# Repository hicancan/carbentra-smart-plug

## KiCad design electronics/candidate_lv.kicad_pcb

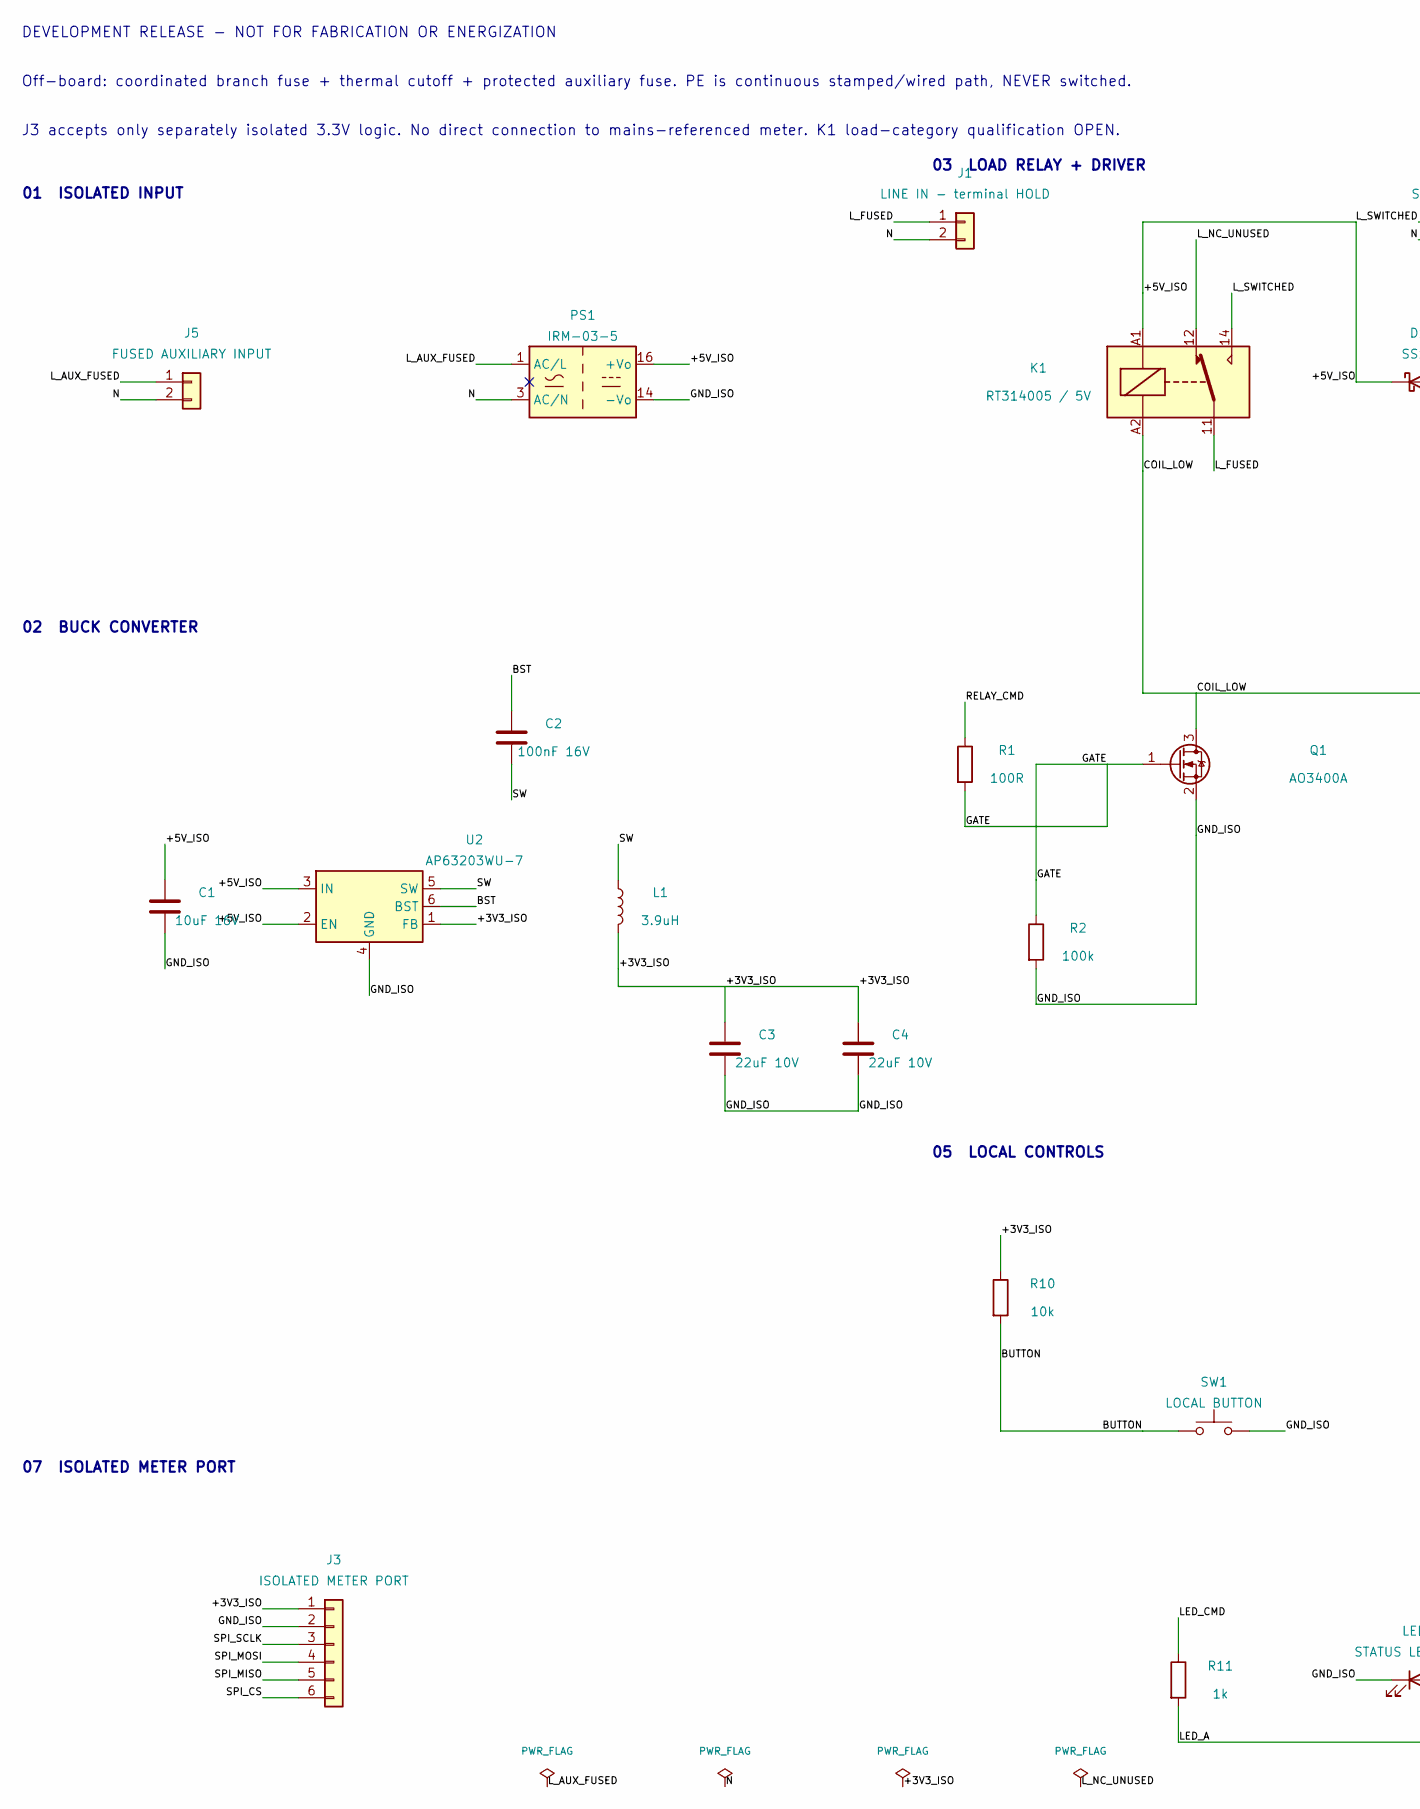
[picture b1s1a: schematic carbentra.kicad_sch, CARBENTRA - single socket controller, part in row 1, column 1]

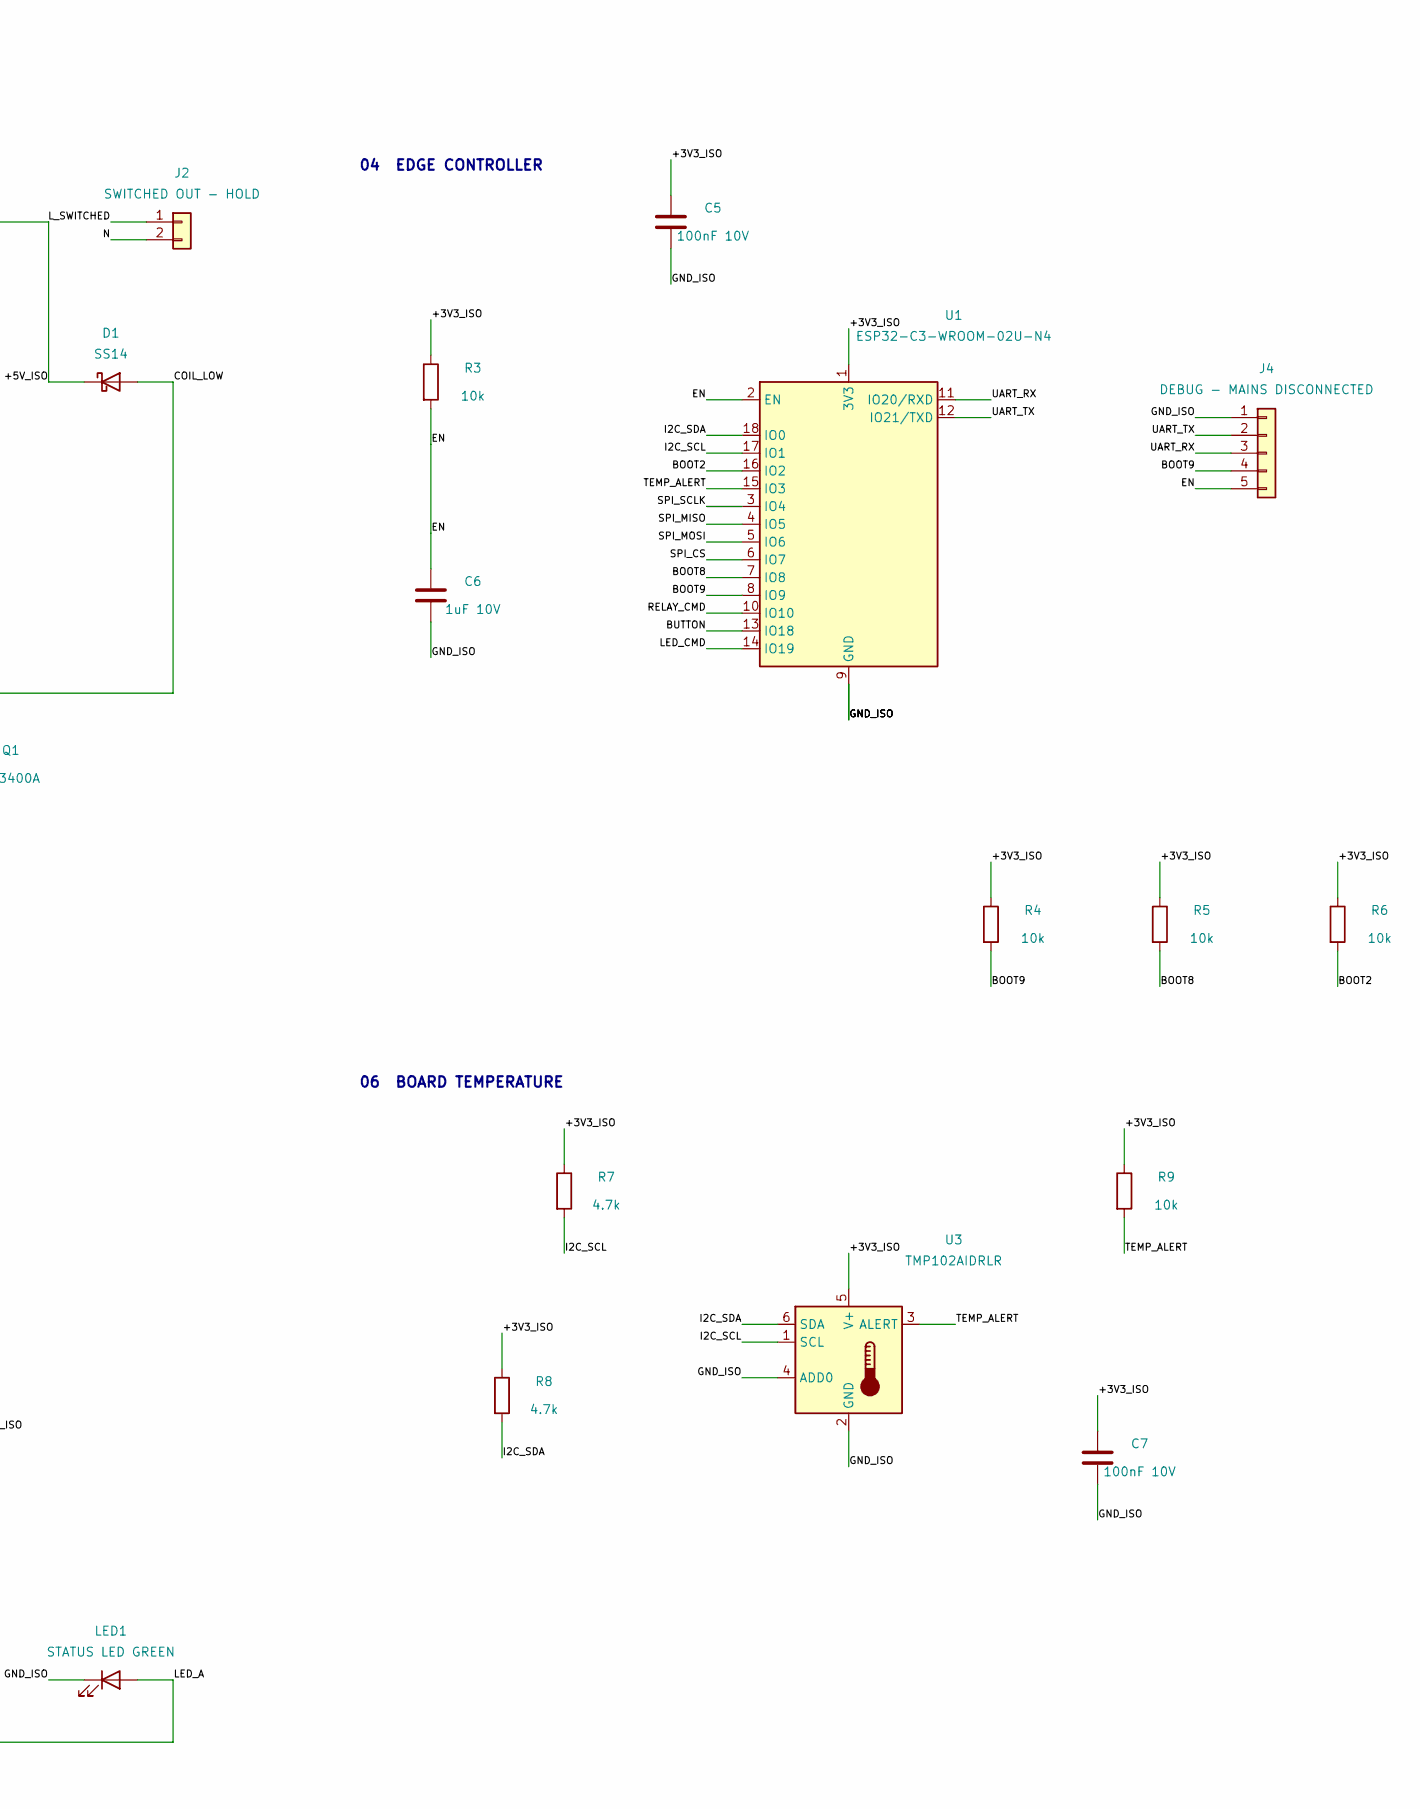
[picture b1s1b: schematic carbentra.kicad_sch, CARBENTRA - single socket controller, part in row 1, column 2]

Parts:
C1: 10uF 16V; C_0805_2012Metric
C2: 100nF 16V; C_0805_2012Metric
C3, C4: 22uF 10V; C_0805_2012Metric
C5, C7: 100nF 10V; C_0805_2012Metric
C6: 1uF 10V; C_0805_2012Metric
D1: SS14; D_SMA
J1: LINE IN - terminal HOLD; TerminalBlock_Phoenix_MKDS-3-2-5.08_1x02_P5.08mm_Horizontal
J2: SWITCHED OUT - HOLD; TerminalBlock_Phoenix_MKDS-3-2-5.08_1x02_P5.08mm_Horizontal
J3: ISOLATED METER PORT; PinHeader_1x06_P2.54mm_Vertical
J4: DEBUG - MAINS DISCONNECTED; PinHeader_1x05_P2.54mm_Vertical
J5: FUSED AUXILIARY INPUT; TerminalBlock_Phoenix_MKDS-3-2-5.08_1x02_P5.08mm_Horizontal
K1: RT314005 / 5V; Relay_SPDT_Schrack-RT1-16A-FormC_RM5mm
L1: 3.9uH; L_Bourns-SRN4018
LED1: STATUS LED GREEN; LED_D3.0mm
PS1: IRM-03-5; Converter_ACDC_MeanWell_IRM-03-xx_THT
Q1: AO3400A; SOT-23
R1: 100R; R_0603_1608Metric
R2: 100k; R_0603_1608Metric
R3, R4, R5, R6, R9, R10: 10k; R_0603_1608Metric
R7, R8: 4.7k; R_0603_1608Metric
R11: 1k; R_0603_1608Metric
SW1: LOCAL BUTTON; SW_PUSH_6mm
U1: ESP32-C3-WROOM-02U-N4; ESP32-C3-WROOM-02U
U2: AP63203WU-7; TSOT-23-6
U3: TMP102AIDRLR; SOT-563

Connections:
+3V3_ISO: C3.1, C4.1, C5.1, C7.1, J3.1, L1.2, R3.1, R4.1, R5.1, R6.1, R7.1, R8.1, R9.1, R10.1, U1.1 (3V3), U2.1 (FB), U3.5 (V+)
+5V_ISO: C1.1, D1.1 (K), K1.A1, PS1.16 (+Vo), U2.2 (EN), U2.3 (IN)
BOOT2: R6.2, U1.16 (IO2)
BOOT8: R5.2, U1.7 (IO8)
BOOT9: J4.4, R4.2, U1.8 (IO9)
BST: C2.1, U2.6 (BST)
BUTTON: R10.2, SW1.1, U1.13 (IO18)
COIL_LOW: D1.2 (A), K1.A2, Q1.3 (D)
EN: C6.1, J4.5, R3.2, U1.2 (EN)
GATE: Q1.1 (G), R1.2, R2.1
GND_ISO: C1.2, C3.2, C4.2, C5.2, C6.2, C7.2, J3.2, J4.1, LED1.1 (K), PS1.14 (-Vo), Q1.2 (S), R2.2, SW1.2, U1.9 (GND), U1.19 (GND), U2.4 (GND), U3.2 (GND), U3.4 (ADD0)
I2C_SCL: R7.2, U1.17 (IO1), U3.1 (SCL)
I2C_SDA: R8.2, U1.18 (IO0), U3.6 (SDA)
LED_A: LED1.2 (A), R11.2
LED_CMD: R11.1, U1.14 (IO19)
L_AUX_FUSED: J5.1, PS1.1 (AC/L)
L_FUSED: J1.1, K1.11
L_NC_UNUSED: K1.12
L_SWITCHED: J2.1, K1.14
N: J1.2, J2.2, J5.2, PS1.3 (AC/N)
RELAY_CMD: R1.1, U1.10 (IO10)
SPI_CS: J3.6, U1.6 (IO7)
SPI_MISO: J3.5, U1.4 (IO5)
SPI_MOSI: J3.4, U1.5 (IO6)
SPI_SCLK: J3.3, U1.3 (IO4)
SW: C2.2, L1.1, U2.5 (SW)
TEMP_ALERT: R9.2, U1.15 (IO3), U3.3 (ALERT)
UART_RX: J4.3, U1.11 (IO20/RXD)
UART_TX: J4.2, U1.12 (IO21/TXD)

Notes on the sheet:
DEVELOPMENT RELEASE - NOT FOR FABRICATION OR ENERGIZATION
Off-board: coordinated branch fuse + thermal cutoff + protected auxiliary fuse. PE is continuous stamped/wired path, NEVER switched.
J3 accepts only separately isolated 3.3V logic. No direct connection to mains-referenced meter. K1 load-category qualification OPEN.
01 ISOLATED INPUT
02 BUCK CONVERTER
03 LOAD RELAY + DRIVER
04 EDGE CONTROLLER
05 LOCAL CONTROLS
06 BOARD TEMPERATURE
07 ISOLATED METER PORT

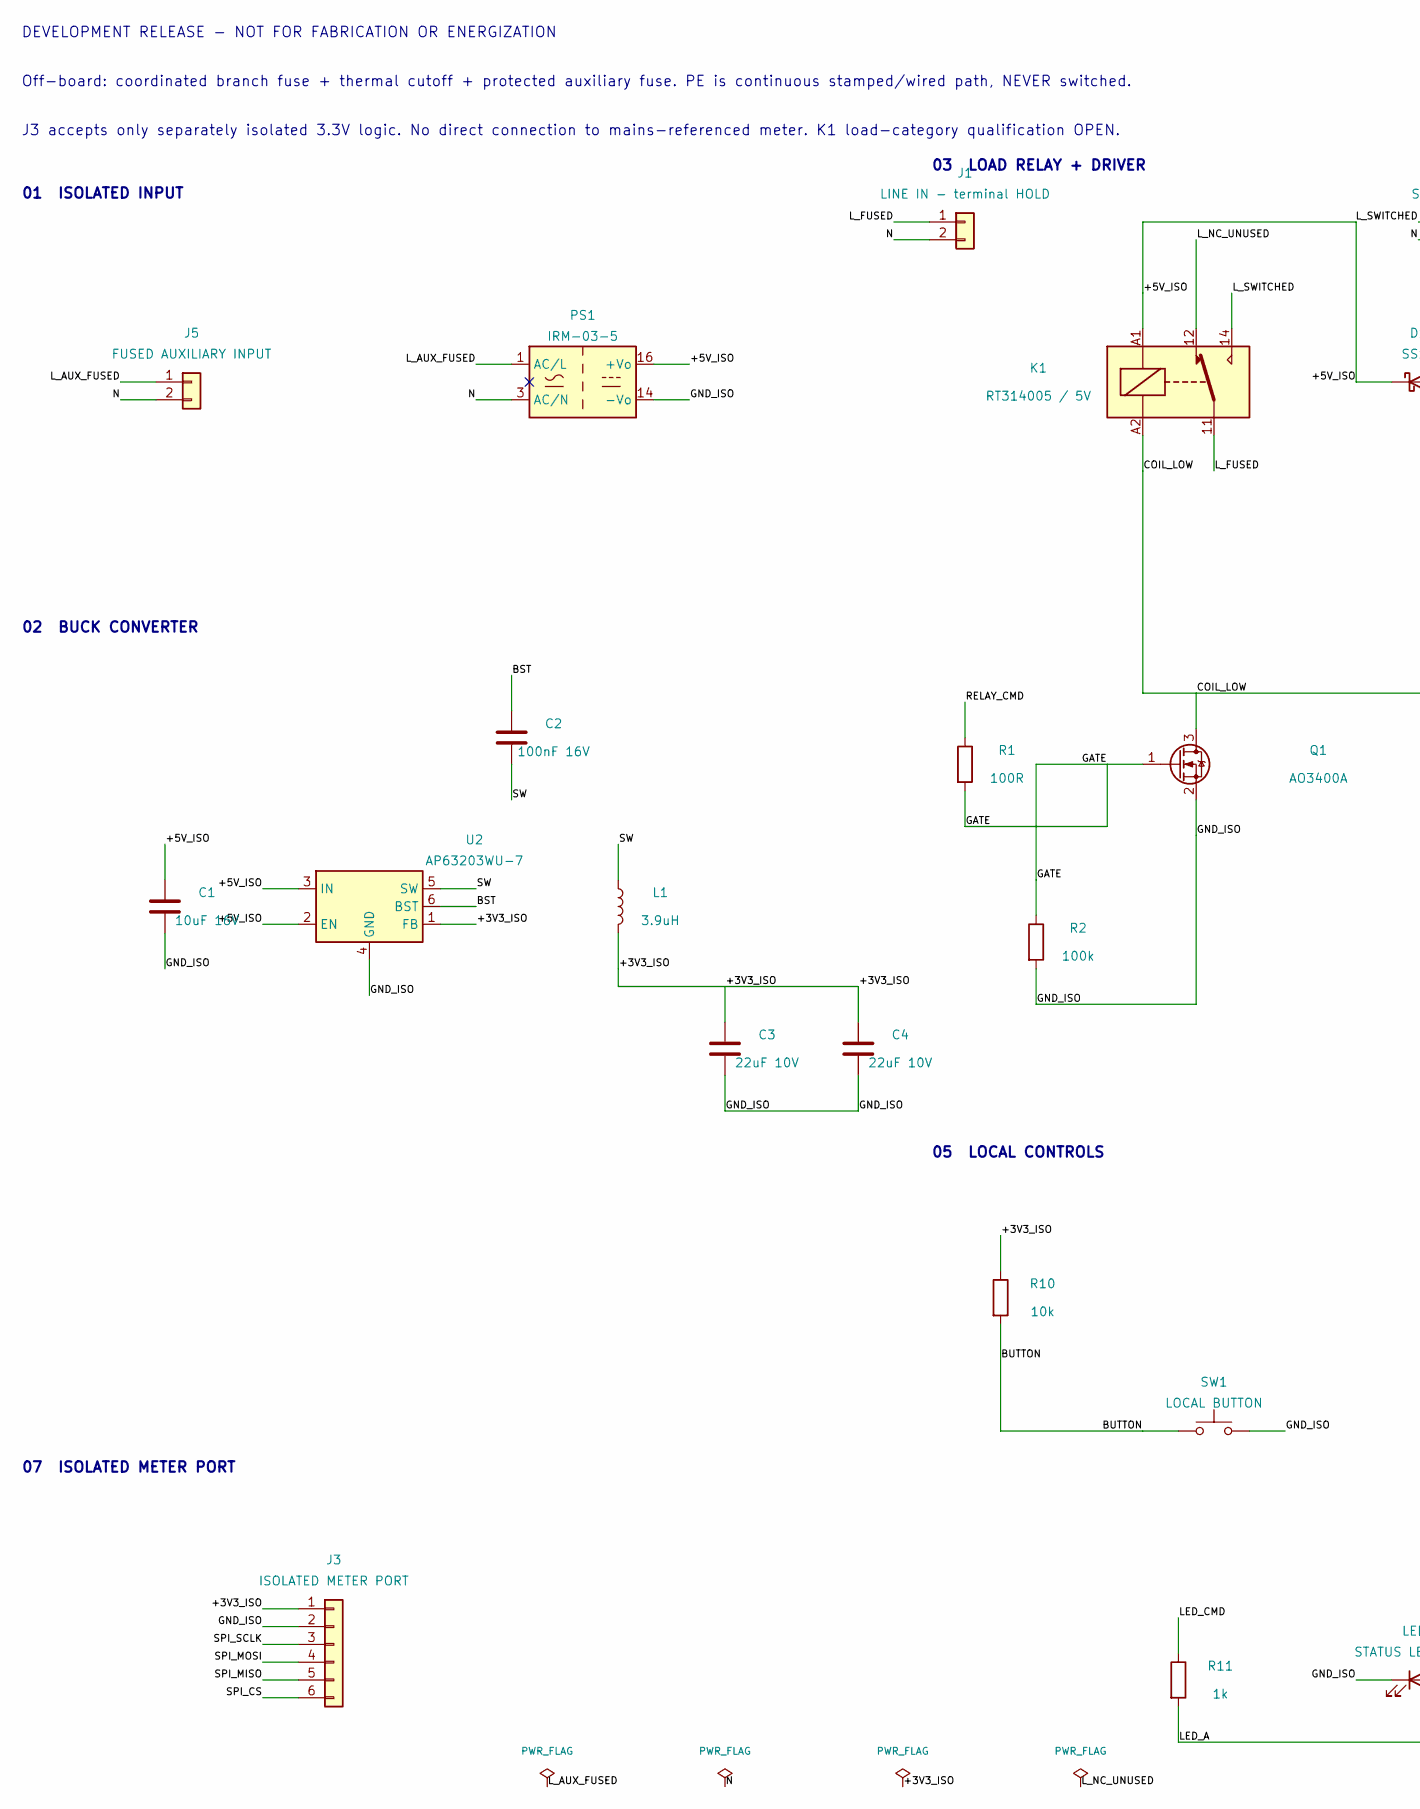
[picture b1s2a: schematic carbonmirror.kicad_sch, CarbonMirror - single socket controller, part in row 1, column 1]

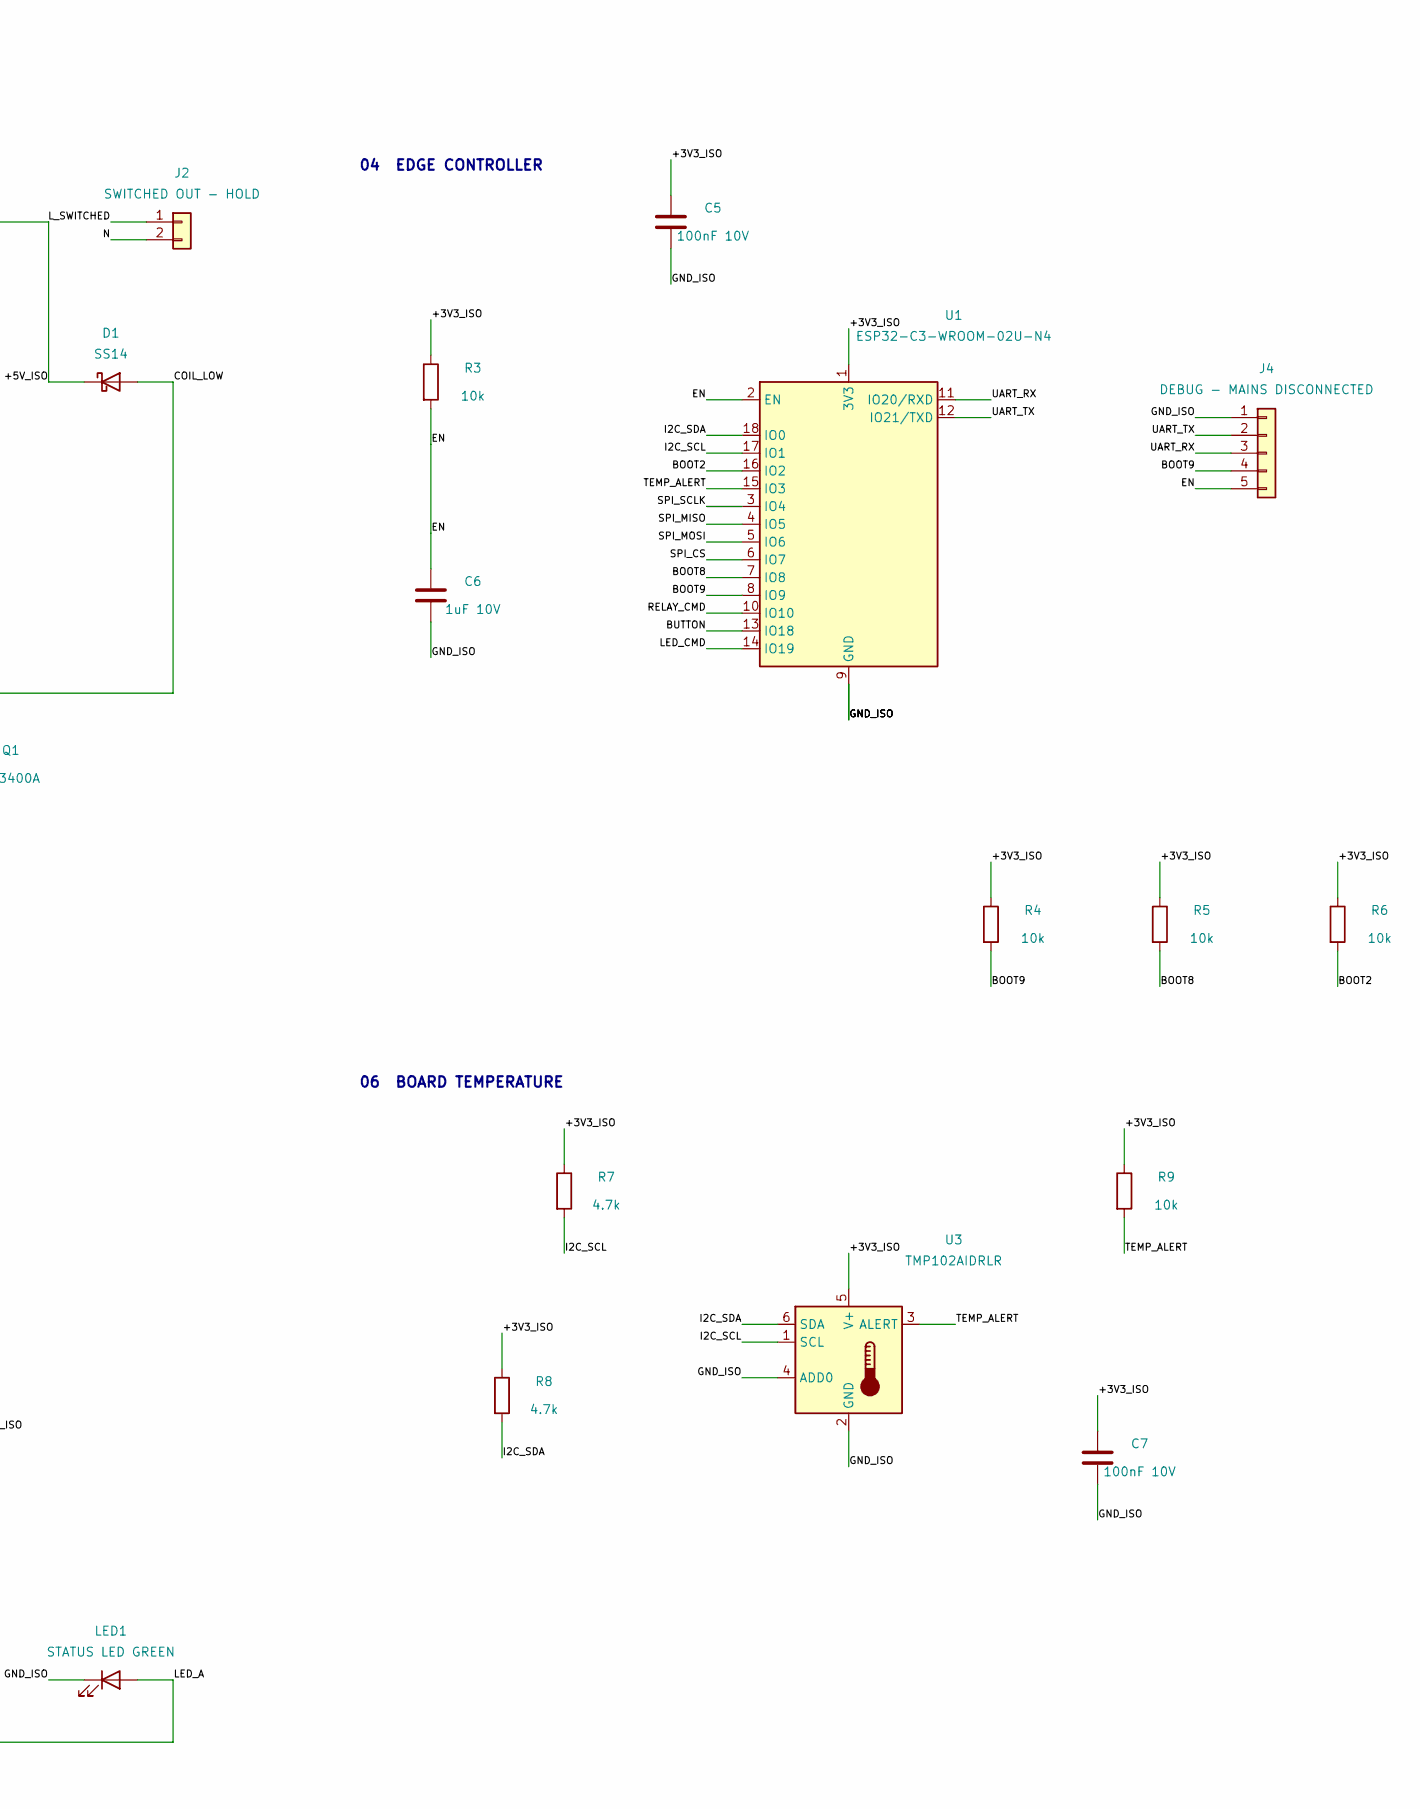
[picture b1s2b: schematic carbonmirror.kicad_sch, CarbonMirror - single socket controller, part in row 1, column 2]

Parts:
C1: 10uF 16V; C_0805_2012Metric
C2: 100nF 16V; C_0805_2012Metric
C3, C4: 22uF 10V; C_0805_2012Metric
C5, C7: 100nF 10V; C_0805_2012Metric
C6: 1uF 10V; C_0805_2012Metric
D1: SS14; D_SMA
J1: LINE IN - terminal HOLD; TerminalBlock_Phoenix_MKDS-3-2-5.08_1x02_P5.08mm_Horizontal
J2: SWITCHED OUT - HOLD; TerminalBlock_Phoenix_MKDS-3-2-5.08_1x02_P5.08mm_Horizontal
J3: ISOLATED METER PORT; PinHeader_1x06_P2.54mm_Vertical
J4: DEBUG - MAINS DISCONNECTED; PinHeader_1x05_P2.54mm_Vertical
J5: FUSED AUXILIARY INPUT; TerminalBlock_Phoenix_MKDS-3-2-5.08_1x02_P5.08mm_Horizontal
K1: RT314005 / 5V; Relay_SPDT_Schrack-RT1-16A-FormC_RM5mm
L1: 3.9uH; L_Bourns-SRN4018
LED1: STATUS LED GREEN; LED_D3.0mm
PS1: IRM-03-5; Converter_ACDC_MeanWell_IRM-03-xx_THT
Q1: AO3400A; SOT-23
R1: 100R; R_0603_1608Metric
R2: 100k; R_0603_1608Metric
R3, R4, R5, R6, R9, R10: 10k; R_0603_1608Metric
R7, R8: 4.7k; R_0603_1608Metric
R11: 1k; R_0603_1608Metric
SW1: LOCAL BUTTON; SW_PUSH_6mm
U1: ESP32-C3-WROOM-02U-N4; ESP32-C3-WROOM-02U
U2: AP63203WU-7; TSOT-23-6
U3: TMP102AIDRLR; SOT-563

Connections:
+3V3_ISO: C3.1, C4.1, C5.1, C7.1, J3.1, L1.2, R3.1, R4.1, R5.1, R6.1, R7.1, R8.1, R9.1, R10.1, U1.1 (3V3), U2.1 (FB), U3.5 (V+)
+5V_ISO: C1.1, D1.1 (K), K1.A1, PS1.16 (+Vo), U2.2 (EN), U2.3 (IN)
BOOT2: R6.2, U1.16 (IO2)
BOOT8: R5.2, U1.7 (IO8)
BOOT9: J4.4, R4.2, U1.8 (IO9)
BST: C2.1, U2.6 (BST)
BUTTON: R10.2, SW1.1, U1.13 (IO18)
COIL_LOW: D1.2 (A), K1.A2, Q1.3 (D)
EN: C6.1, J4.5, R3.2, U1.2 (EN)
GATE: Q1.1 (G), R1.2, R2.1
GND_ISO: C1.2, C3.2, C4.2, C5.2, C6.2, C7.2, J3.2, J4.1, LED1.1 (K), PS1.14 (-Vo), Q1.2 (S), R2.2, SW1.2, U1.9 (GND), U1.19 (GND), U2.4 (GND), U3.2 (GND), U3.4 (ADD0)
I2C_SCL: R7.2, U1.17 (IO1), U3.1 (SCL)
I2C_SDA: R8.2, U1.18 (IO0), U3.6 (SDA)
LED_A: LED1.2 (A), R11.2
LED_CMD: R11.1, U1.14 (IO19)
L_AUX_FUSED: J5.1, PS1.1 (AC/L)
L_FUSED: J1.1, K1.11
L_NC_UNUSED: K1.12
L_SWITCHED: J2.1, K1.14
N: J1.2, J2.2, J5.2, PS1.3 (AC/N)
RELAY_CMD: R1.1, U1.10 (IO10)
SPI_CS: J3.6, U1.6 (IO7)
SPI_MISO: J3.5, U1.4 (IO5)
SPI_MOSI: J3.4, U1.5 (IO6)
SPI_SCLK: J3.3, U1.3 (IO4)
SW: C2.2, L1.1, U2.5 (SW)
TEMP_ALERT: R9.2, U1.15 (IO3), U3.3 (ALERT)
UART_RX: J4.3, U1.11 (IO20/RXD)
UART_TX: J4.2, U1.12 (IO21/TXD)

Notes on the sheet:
DEVELOPMENT RELEASE - NOT FOR FABRICATION OR ENERGIZATION
Off-board: coordinated branch fuse + thermal cutoff + protected auxiliary fuse. PE is continuous stamped/wired path, NEVER switched.
J3 accepts only separately isolated 3.3V logic. No direct connection to mains-referenced meter. K1 load-category qualification OPEN.
01 ISOLATED INPUT
02 BUCK CONVERTER
03 LOAD RELAY + DRIVER
04 EDGE CONTROLLER
05 LOCAL CONTROLS
06 BOARD TEMPERATURE
07 ISOLATED METER PORT

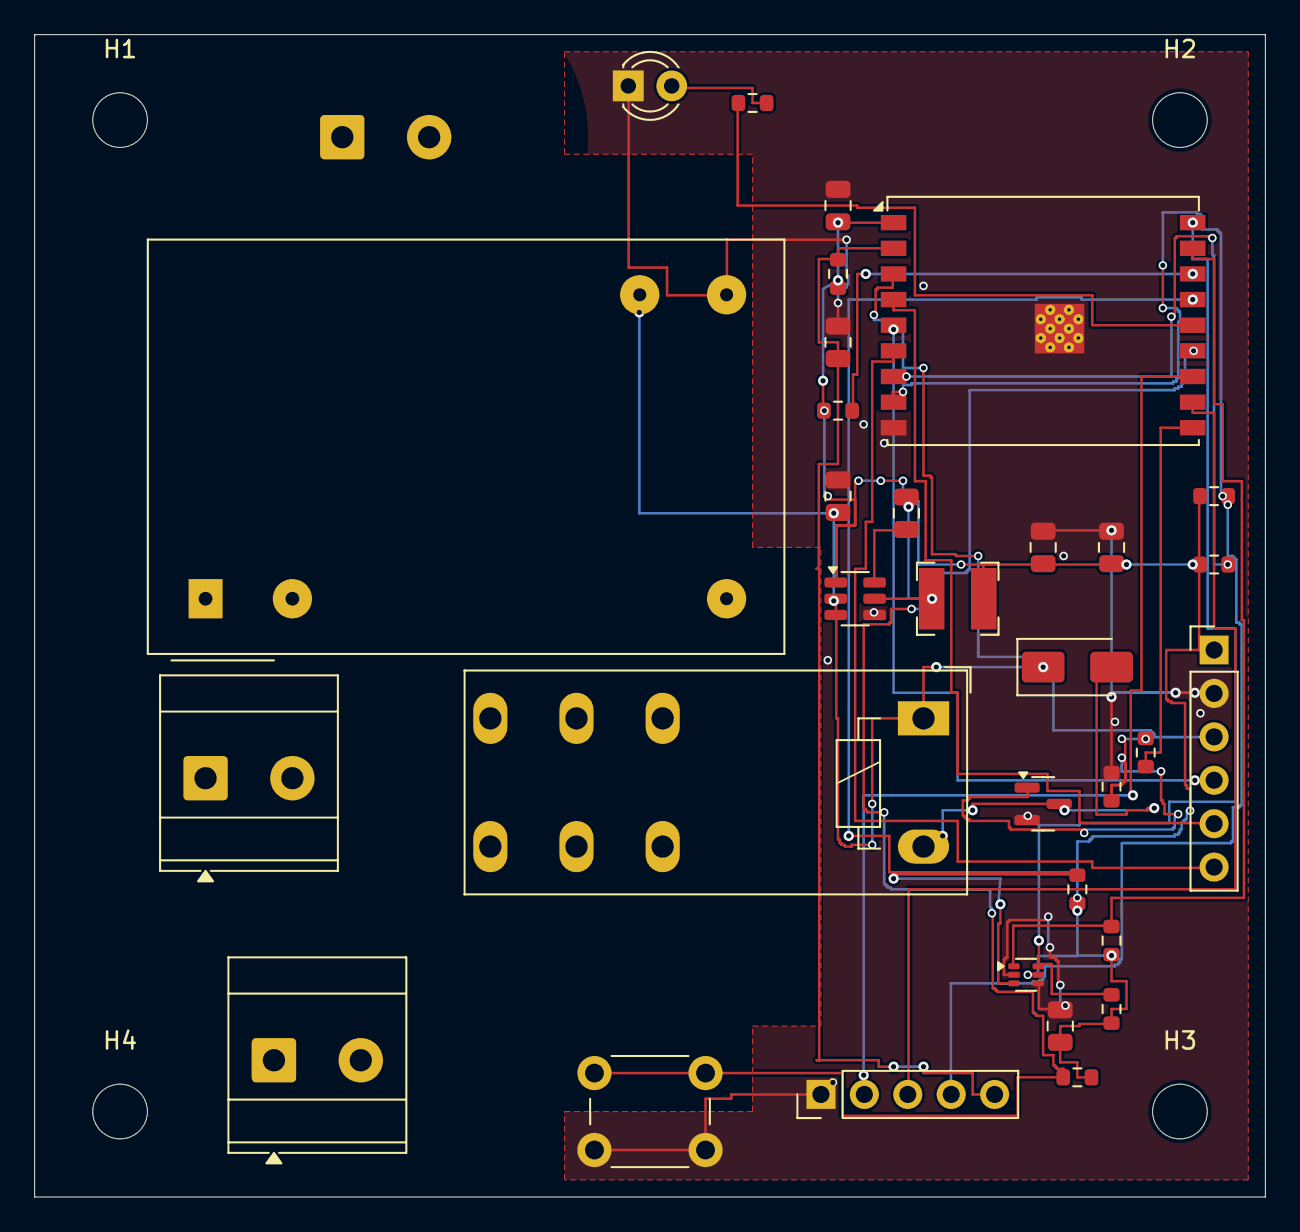
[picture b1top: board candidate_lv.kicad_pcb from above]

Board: 2 copper layers, 72.0 x 68.0 mm, 37 parts (0 on the bottom side), 28 nets.

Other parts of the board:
H1, H2, H3, H4: MountingHole_3.2mm_M3

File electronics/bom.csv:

Reference,Value,Manufacturer part candidate,Footprint,Source URL,Status
PS1,IRM-03-5,IRM-03-5,Converter_ACDC:Converter_ACDC_MeanWell_IRM-03-xx_THT,https://www.meanwell.com/Upload/PDF/IRM-03/IRM-03-SPEC.PDF,"UNRELEASED: verify exact variant, sourcing and application"
K1,RT314005 / 5V,RT314005 / 1-1649328-0,Relay_THT:Relay_SPDT_Schrack-RT1-16A-FormC_RM5mm,https://www.te.com/en/product-1-1649328-0.html,"UNRELEASED: verify exact variant, sourcing and application"
U1,ESP32-C3-WROOM-02U-N4,ESP32-C3-WROOM-02U-N4,RF_Module:ESP32-C3-WROOM-02U,https://www.espressif.com/sites/default/files/documentation/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,"UNRELEASED: verify exact variant, sourcing and application"
U2,AP63203WU-7,AP63203WU-7,Package_TO_SOT_SMD:TSOT-23-6,https://www.diodes.com/datasheet/download/AP63200-AP63201-AP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,"UNRELEASED: verify exact variant, sourcing and application"
L1,3.9uH,SRN4018-3R9M,Inductor_SMD:L_Bourns-SRN4018,https://www.bourns.com/docs/product-datasheets/srn4018.pdf,"UNRELEASED: verify exact variant, sourcing and application"
C1,10uF 16V,GRM21-series candidate,Capacitor_SMD:C_0805_2012Metric,https://www.murata.com/en-us/products/capacitor/ceramiccapacitor,"UNRELEASED: verify exact variant, sourcing and application"
C2,100nF 16V,GRM21-series candidate,Capacitor_SMD:C_0805_2012Metric,https://www.murata.com/en-us/products/capacitor/ceramiccapacitor,"UNRELEASED: verify exact variant, sourcing and application"
C3,22uF 10V,GRM21-series candidate,Capacitor_SMD:C_0805_2012Metric,https://www.murata.com/en-us/products/capacitor/ceramiccapacitor,"UNRELEASED: verify exact variant, sourcing and application"
C4,22uF 10V,GRM21-series candidate,Capacitor_SMD:C_0805_2012Metric,https://www.murata.com/en-us/products/capacitor/ceramiccapacitor,"UNRELEASED: verify exact variant, sourcing and application"
C5,100nF 10V,GRM21-series candidate,Capacitor_SMD:C_0805_2012Metric,https://www.murata.com/en-us/products/capacitor/ceramiccapacitor,"UNRELEASED: verify exact variant, sourcing and application"
Q1,AO3400A,AO3400A,Package_TO_SOT_SMD:SOT-23,https://www.aosmd.com/res/data_sheets/AO3400A.pdf,"UNRELEASED: verify exact variant, sourcing and application"
D1,SS14,SS14,Diode_SMD:D_SMA,https://www.vishay.com/docs/88746/ss12.pdf,"UNRELEASED: verify exact variant, sourcing and application"
R1,100R,RC0603FR-07100RL,Resistor_SMD:R_0603_1608Metric,https://www.yageo.com/en/ProductSearch,"UNRELEASED: verify exact variant, sourcing and application"
R2,100k,RC0603FR-07100KL,Resistor_SMD:R_0603_1608Metric,https://www.yageo.com/en/ProductSearch,"UNRELEASED: verify exact variant, sourcing and application"
R3,10k,RC0603FR-0710KL,Resistor_SMD:R_0603_1608Metric,https://www.yageo.com/en/ProductSearch,"UNRELEASED: verify exact variant, sourcing and application"
C6,1uF 10V,GRM21-series candidate,Capacitor_SMD:C_0805_2012Metric,https://www.murata.com/en-us/products/capacitor/ceramiccapacitor,"UNRELEASED: verify exact variant, sourcing and application"
R4,10k,RC0603FR-0710KL,Resistor_SMD:R_0603_1608Metric,https://www.yageo.com/en/ProductSearch,"UNRELEASED: verify exact variant, sourcing and application"
R5,10k,RC0603FR-0710KL,Resistor_SMD:R_0603_1608Metric,https://www.yageo.com/en/ProductSearch,"UNRELEASED: verify exact variant, sourcing and application"
R6,10k,RC0603FR-0710KL,Resistor_SMD:R_0603_1608Metric,https://www.yageo.com/en/ProductSearch,"UNRELEASED: verify exact variant, sourcing and application"
U3,TMP102AIDRLR,TMP102AIDRLR,Package_TO_SOT_SMD:SOT-563,https://www.ti.com/lit/ds/symlink/tmp102.pdf,"UNRELEASED: verify exact variant, sourcing and application"
R7,4.7k,RC0603FR-074K7L,Resistor_SMD:R_0603_1608Metric,https://www.yageo.com/en/ProductSearch,"UNRELEASED: verify exact variant, sourcing and application"
R8,4.7k,RC0603FR-074K7L,Resistor_SMD:R_0603_1608Metric,https://www.yageo.com/en/ProductSearch,"UNRELEASED: verify exact variant, sourcing and application"
R9,10k,RC0603FR-0710KL,Resistor_SMD:R_0603_1608Metric,https://www.yageo.com/en/ProductSearch,"UNRELEASED: verify exact variant, sourcing and application"
C7,100nF 10V,GRM21-series candidate,Capacitor_SMD:C_0805_2012Metric,https://www.murata.com/en-us/products/capacitor/ceramiccapacitor,"UNRELEASED: verify exact variant, sourcing and application"
J1,LINE IN - terminal HOLD,1711725,TerminalBlock_Phoenix:TerminalBlock_Phoenix_MKDS-3-2-5.08_1x02_P5.08mm_Horizontal,https://www.phoenixcontact.com/en-pc/products/pcb-terminal-b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,"UNRELEASED: verify exact variant, sourcing and application"
J2,SWITCHED OUT - HOLD,1711725,TerminalBlock_Phoenix:TerminalBlock_Phoenix_MKDS-3-2-5.08_1x02_P5.08mm_Horizontal,https://www.phoenixcontact.com/en-pc/products/pcb-terminal-b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,"UNRELEASED: verify exact variant, sourcing and application"
J3,ISOLATED METER PORT,Samtec TSW-1xx-07 candidate,Connector_PinHeader_2.54mm:PinHeader_1x06_P2.54mm_Vertical,https://www.samtec.com/products/tsw,"UNRELEASED: verify exact variant, sourcing and application"
J4,DEBUG - MAINS DISCONNECTED,Samtec TSW-1xx-07 candidate,Connector_PinHeader_2.54mm:PinHeader_1x05_P2.54mm_Vertical,https://www.samtec.com/products/tsw,"UNRELEASED: verify exact variant, sourcing and application"
J5,FUSED AUXILIARY INPUT,1711725,TerminalBlock_Phoenix:TerminalBlock_Phoenix_MKDS-3-2-5.08_1x02_P5.08mm_Horizontal,https://www.phoenixcontact.com/en-pc/products/pcb-terminal-b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,"UNRELEASED: verify exact variant, sourcing and application"
SW1,LOCAL BUTTON,B3F-1000 candidate,Button_Switch_THT:SW_PUSH_6mm,https://components.omron.com/us-en/products/switches/B3F,"UNRELEASED: verify exact variant, sourcing and application"
LED1,STATUS LED GREEN,WP710A10GD candidate,LED_THT:LED_D3.0mm,https://www.kingbrightusa.com/,"UNRELEASED: verify exact variant, sourcing and application"
R10,10k,RC0603FR-0710KL,Resistor_SMD:R_0603_1608Metric,https://www.yageo.com/en/ProductSearch,"UNRELEASED: verify exact variant, sourcing and application"
R11,1k,RC0603FR-071KL,Resistor_SMD:R_0603_1608Metric,https://www.yageo.com/en/ProductSearch,"UNRELEASED: verify exact variant, sourcing and application"
